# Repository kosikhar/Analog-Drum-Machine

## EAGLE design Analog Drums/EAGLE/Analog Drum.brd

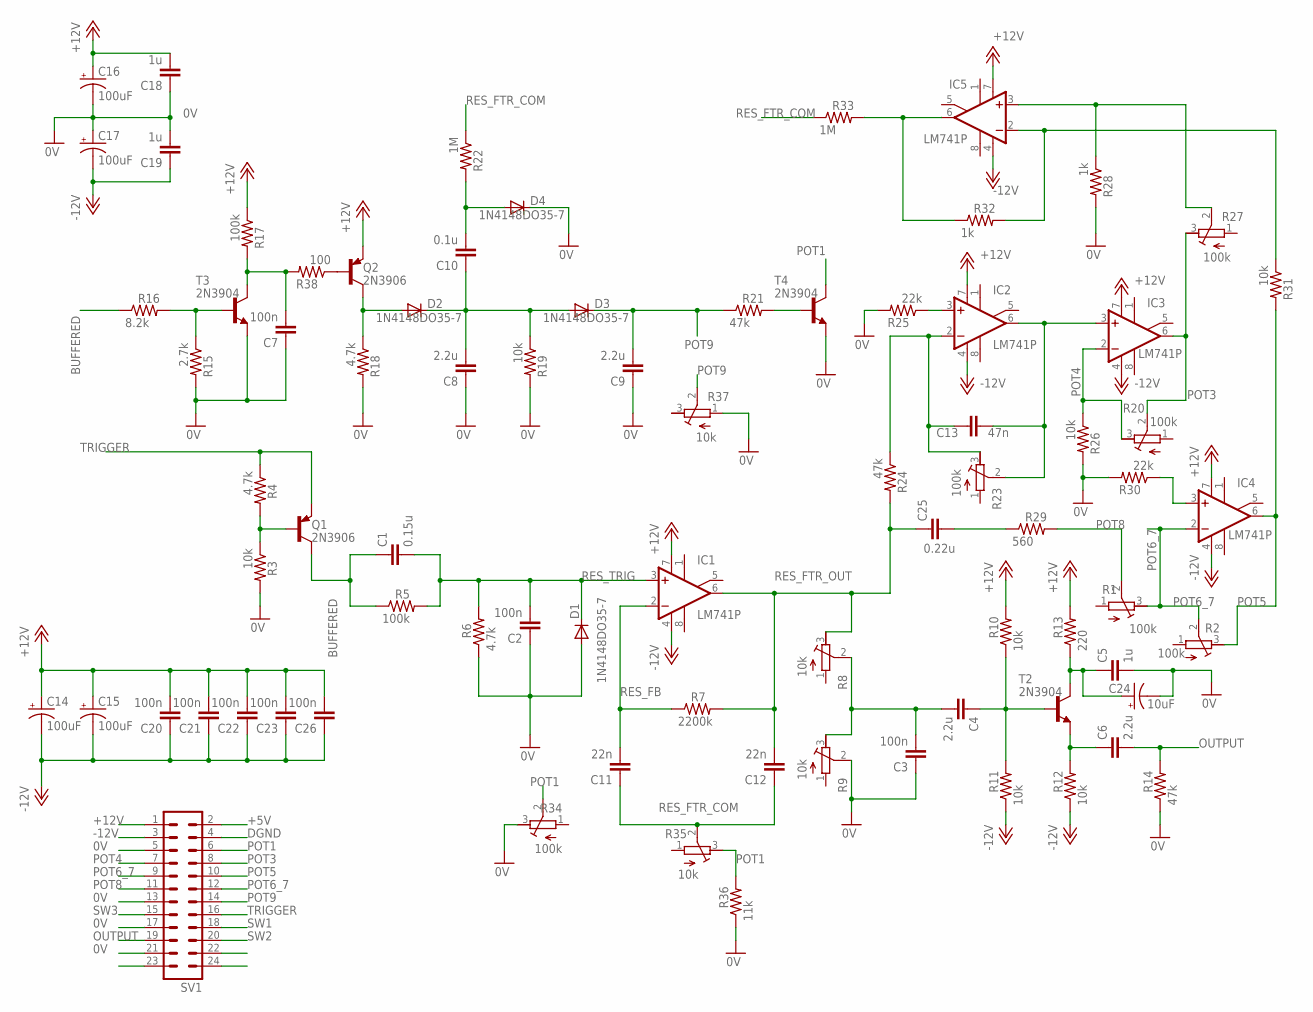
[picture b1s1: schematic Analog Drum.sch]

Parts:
C1: 0.15u; C050-024X044
C2, C3, C7, C20, C21, C22, C23, C26: 100n; C050-024X044
C4, C6, C8, C9: 2.2u; C050-024X044
C5, C18, C19: 1u; C050-024X044
C10: 0.1u; C050-024X044
C11, C12: 22n; C050-024X044
C13: 47n; C050-024X044
C14, C15, C16, C17: 100uF; E5-8,5
C24: 10uF; E2,5-6
C25: 0.22u; C050-024X044
D1, D2, D3, D4: 1N4148DO35-7; DO35-7
IC1, IC2, IC3, IC4, IC5: LM741P; DIL08
Q1, Q2: 2N3906; TO92
R1, R2, R20, R23, R27, R34: 100k; RTRIM64W
R3, R10, R11, R12, R19, R26, R31: 10k; 0207/10
R4, R6, R18: 4.7k; 0207/10
R5, R17: 100k; 0207/10
R7: 2200k; 0207/10
R8, R9, R35, R37: 10k; RTRIM64W
R13: 220; 0207/10
R14, R21, R24: 47k; 0207/10
R15: 2.7k; 0207/10
R16: 8.2k; 0207/10
R22, R33: 1M; 0207/10
R25, R30: 22k; 0207/10
R28, R32: 1k; 0207/10
R29: 560; 0207/10
R36: 11k; 0207/10
R38: 100; 0207/10
SV1: MA12-2
T2, T3, T4: 2N3904; TO92

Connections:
0V: C2.1, C3.1, C5.2, C7.1, C8.1, C9.1, C16.-, C17.+, C18.1, C19.2, C24.-, D1.A, D4.C, R3.2, R6.1, R9.2 (S), R14.1, R15.2, R18.2, R19.2, R25.2, R26.2, R28.2, R30.2, R34.3 (E), R36.1, R37.1 (A), SV1.5, SV1.13, SV1.17, SV1.21, T3.3 (E), T4.3 (E)
+5V: SV1.2
+12V: C14.+, C15.+, C16.+, C18.2, C20.2, C21.2, C22.2, C23.2, C26.2, IC1.7 (V+), IC2.7 (V+), IC3.7 (V+), IC4.7 (V+), IC5.7 (V+), Q2.3 (E), R10.2, R13.2, R17.1, SV1.1
-12V: C14.-, C15.-, C17.-, C19.1, C20.1, C21.1, C22.1, C23.1, C26.1, IC1.4 (V-), IC2.4 (V-), IC3.4 (V-), IC4.4 (V-), IC5.4 (V-), R11.1, R12.1, SV1.3
BUFFERED: C1.1, Q1.1 (C), R5.1, R16.1
DGND: SV1.4
unnamed: C25.2, R29.1
unnamed: IC4.3 (+IN), R30.1
unnamed: Q1.2 (B), R3.1, R4.2
unnamed: C10.2, D4.A, R22.2
unnamed: Q2.2 (B), R38.1
unnamed: IC2.3 (+IN), R25.1
unnamed: C3.2, C4.2, R8.2 (S), R9.3 (E)
unnamed: C4.1, R10.1, R11.2, T2.2 (B)
unnamed: C6.1, R12.2, T2.3 (E)
unnamed: C5.1, C24.+, R13.1, T2.1 (C)
unnamed: C13.2, IC2.2 (-IN), R23.3 (E), R24.1
unnamed: R15.1, R16.2, T3.2 (B)
unnamed: C7.2, R17.2, R38.2, T3.1 (C)
unnamed: D2.A, Q2.1 (C), R18.1
unnamed: C8.2, C10.1, D2.C, D3.A, R19.1
unnamed: R21.2, T4.2 (B)
unnamed: C13.1, IC2.6 (OUT), IC3.3 (+IN), R23.2 (S)
unnamed: IC5.3 (+IN), R27.2 (S), R28.1
unnamed: IC5.2 (-IN), R31.1, R32.2
unnamed: IC5.6 (OUT), R32.1, R33.2
OUTPUT: C6.2, R14.2, SV1.19
POT1: R34.2 (S), R35.3 (E), R36.2, SV1.6, T4.1 (C)
POT3: IC3.6 (OUT), R20.2 (S), R27.3 (E), SV1.8
POT4: IC3.2 (-IN), R20.3 (E), R26.1, SV1.7
POT5: IC4.6 (OUT), R2.3 (E), R31.2, SV1.10
POT6_7: IC4.2 (-IN), R1.3 (E), R2.2 (S), SV1.9, SV1.12
POT8: R1.2 (S), R29.2, SV1.11
POT9: C9.2, D3.C, R21.1, R37.2 (S), SV1.14
RES_FB: C11.2, IC1.2 (-IN), R7.1
RES_FTR_COM: C11.1, C12.1, R22.1, R33.1, R35.2 (S)
RES_FTR_OUT: C12.2, C25.1, IC1.6 (OUT), R7.2, R8.3 (E), R24.2
RES_TRIG: C1.2, C2.2, D1.C, IC1.3 (+IN), R5.2, R6.2
SW1: SV1.18
SW2: SV1.20
SW3: SV1.15
TRIGGER: Q1.3 (E), R4.1, SV1.16

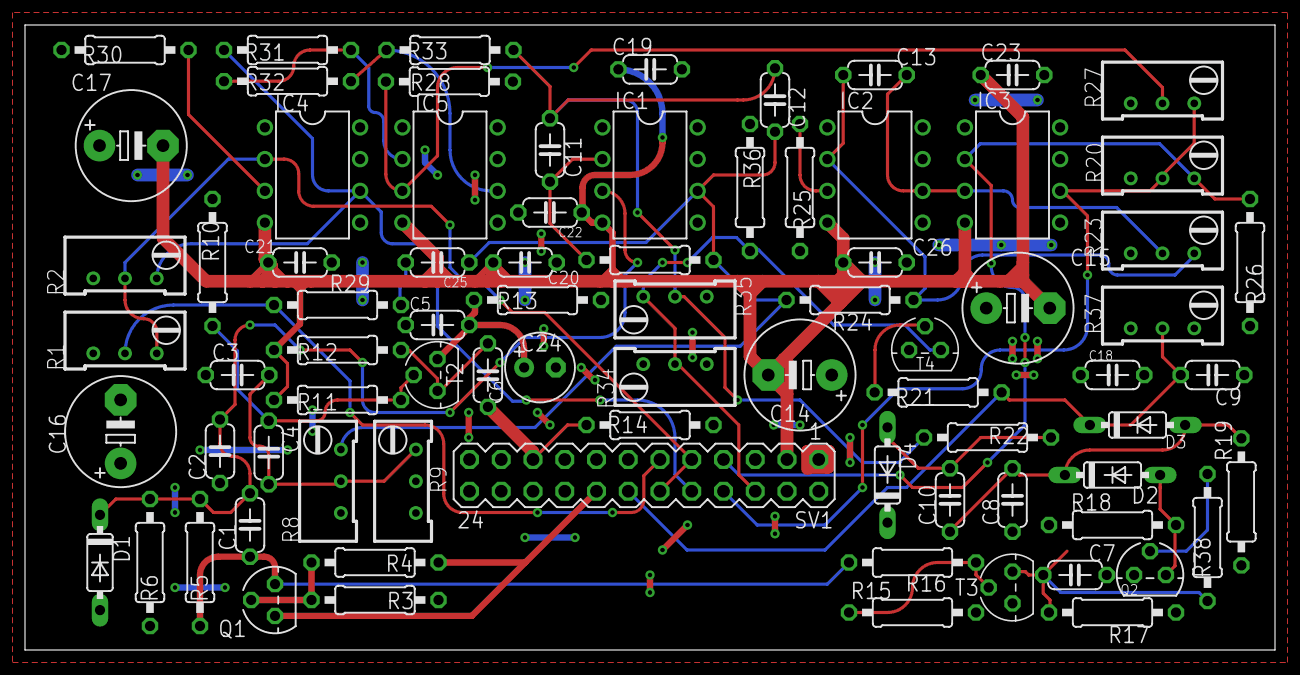
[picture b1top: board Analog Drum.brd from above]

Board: 2 copper layers, 100.0 x 50.0 mm, 79 parts (0 on the bottom side), 37 nets.

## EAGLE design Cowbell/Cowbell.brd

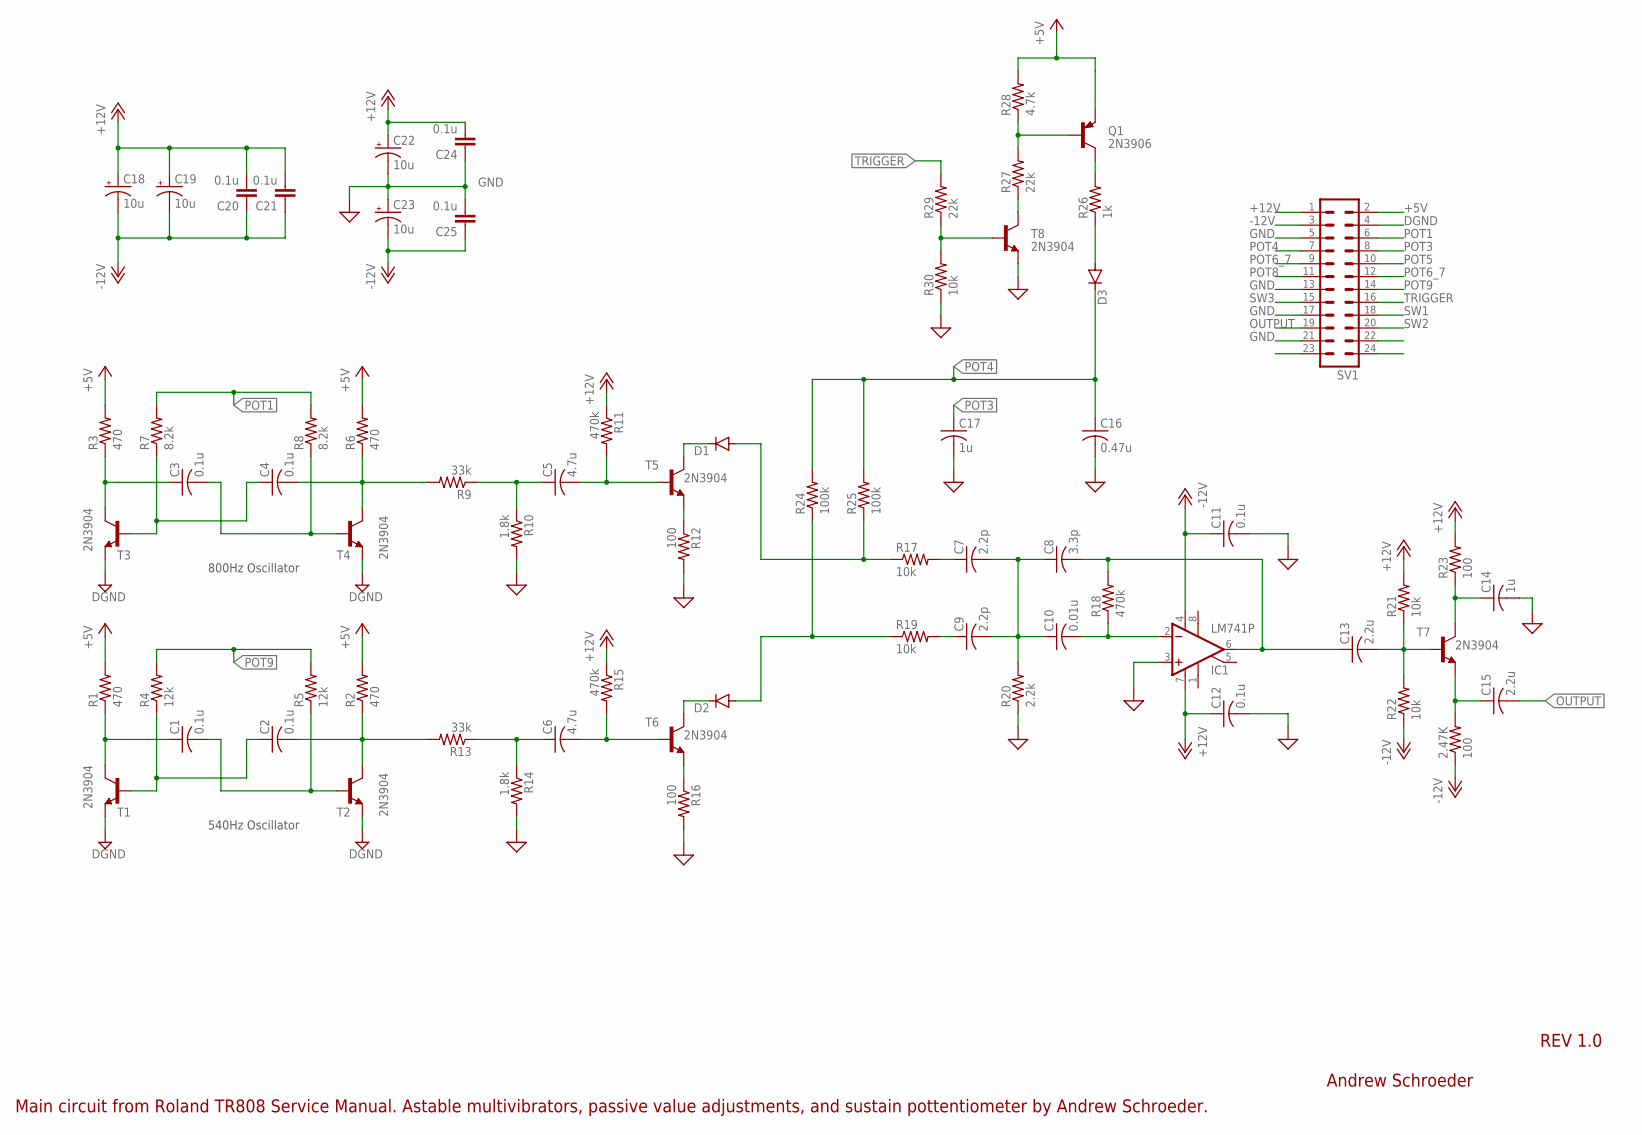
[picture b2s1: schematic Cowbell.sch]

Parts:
2.47K: 100; 0207/7
C1, C2, C3, C4, C11, C12: 0.1u; C025-024X044
C5, C6: 4.7u; C025-024X044
C7, C9: 2.2p; C025-024X044
C8: 3.3p; C025-024X044
C10: 0.01u; C025-024X044
C13, C15: 2.2u; C025-024X044
C14, C17: 1u; C025-024X044
C16: 0.47u; C025-024X044
C18, C19, C22, C23: 10u; E2,5-6
C20, C21, C24, C25: 0.1u; C050-024X044
D1, D2, D3: 1N4148DO35-7; DO35-7
IC1: LM741P; DIL08
Q1: 2N3906; TO92
R1, R2, R3, R6: 470; 0207/7
R4, R5: 12k; 0207/7
R7, R8: 8.2k; 0207/7
R9, R13: 33k; 0207/7
R10, R14: 1.8k; 0207/7
R11, R15, R18: 470k; 0207/7
R12, R16, R23: 100; 0207/7
R17, R19, R21, R22, R30: 10k; 0207/7
R20: 2.2k; 0207/7
R24, R25: 100k; 0207/7
R26: 1k; 0207/7
R27, R29: 22k; 0207/7
R28: 4.7k; 0207/7
SV1: MA12-2
T1, T2, T3, T4, T5, T6, T7, T8: 2N3904; TO92

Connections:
+5V: Q1.3 (E), R1.2, R2.2, R3.2, R6.2, R28.2, SV1.2
+12V: C12.1, C18.+, C19.+, C20.2, C21.2, C22.+, C24.2, IC1.7 (V+), R11.1, R15.1, R21.2, R23.2, SV1.1
-12V: 2.47K.1, C11.1, C18.-, C19.-, C20.1, C21.1, C23.-, C25.1, IC1.4 (V-), R22.1, SV1.3; also elsewhere on the board
DGND: SV1.4, T1.3 (E), T2.3 (E), T3.3 (E), T4.3 (E)
GND: C11.2, C12.2, C14.2, C16.2, C17.2, C22.-, C23.+, C24.1, C25.2, IC1.3 (+IN), R10.2, R12.2, R14.2, R16.2, R20.1, R30.1, SV1.5, SV1.13, SV1.17, SV1.21, T8.3 (E)
unnamed: C4.2, R6.1, R9.2, T4.1 (C)
unnamed: C2.2, R2.1, R13.2, T2.1 (C)
unnamed: C1.1, R1.1, T1.1 (C)
unnamed: C2.1, R4.1, T1.2 (B)
unnamed: C3.1, R3.1, T3.1 (C)
unnamed: C4.1, R7.1, T3.2 (B)
unnamed: C1.2, R5.1, T2.2 (B)
unnamed: C3.2, R8.1, T4.2 (B)
unnamed: C5.1, R9.1, R10.1
unnamed: D1.C, T5.1 (C)
unnamed: C5.2, R11.2, T5.2 (B)
unnamed: R12.1, T5.3 (E)
unnamed: C6.1, R13.1, R14.1
unnamed: C6.2, R15.2, T6.2 (B)
unnamed: R16.1, T6.3 (E)
unnamed: D2.C, T6.1 (C)
unnamed: D1.A, R17.1, R25.1
unnamed: D2.A, R19.1, R24.1
unnamed: C7.1, R17.2
unnamed: C7.2, C8.1, C9.2, C10.1, R20.2
unnamed: C8.2, C13.1, IC1.6 (OUT), R18.2
unnamed: C10.2, IC1.2 (-IN), R18.1
unnamed: C13.2, R21.1, R22.2, T7.2 (B)
unnamed: C9.1, R19.2
unnamed: Q1.1 (C), R26.2
unnamed: C14.1, R23.1, T7.1 (C)
unnamed 34: 2.47K.2, C15.1, T7.3 (E); also elsewhere on the board
unnamed: R27.1, T8.1 (C)
unnamed: D3.A, R26.1
unnamed: R29.1, R30.2, T8.2 (B)
unnamed: Q1.2 (B), R27.2, R28.1
OUTPUT: C15.2, SV1.19
POT1: R7.2, R8.2, SV1.6
POT3: C17.1, SV1.8
POT4: C16.1, D3.C, R24.2, R25.2, SV1.7
POT5: SV1.10
POT6_7: SV1.9, SV1.12
POT8: SV1.11
POT9: R4.2, R5.2, SV1.14
SW1: SV1.18
SW2: SV1.20
SW3: SV1.15
TRIGGER: R29.2, SV1.16

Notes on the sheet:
540Hz Oscillator
800Hz Oscillator
Andrew Schroeder
REV 1.0
Main circuit from Roland TR808 Service Manual. Astable multivibrators, passive value adjustments, and sustain pottentiometer by Andrew Schroeder.

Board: 2 copper layers, 75 parts (0 on the bottom side), 43 nets, no tracks yet.

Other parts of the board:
R31: 2.47k; 0207/7
U$1, U$2, U$3, U$4: STAND-OFF
U$6: A5L-LOC

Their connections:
-12V: R31.1; also elsewhere on the board
unnamed 34: R31.2; also elsewhere on the board

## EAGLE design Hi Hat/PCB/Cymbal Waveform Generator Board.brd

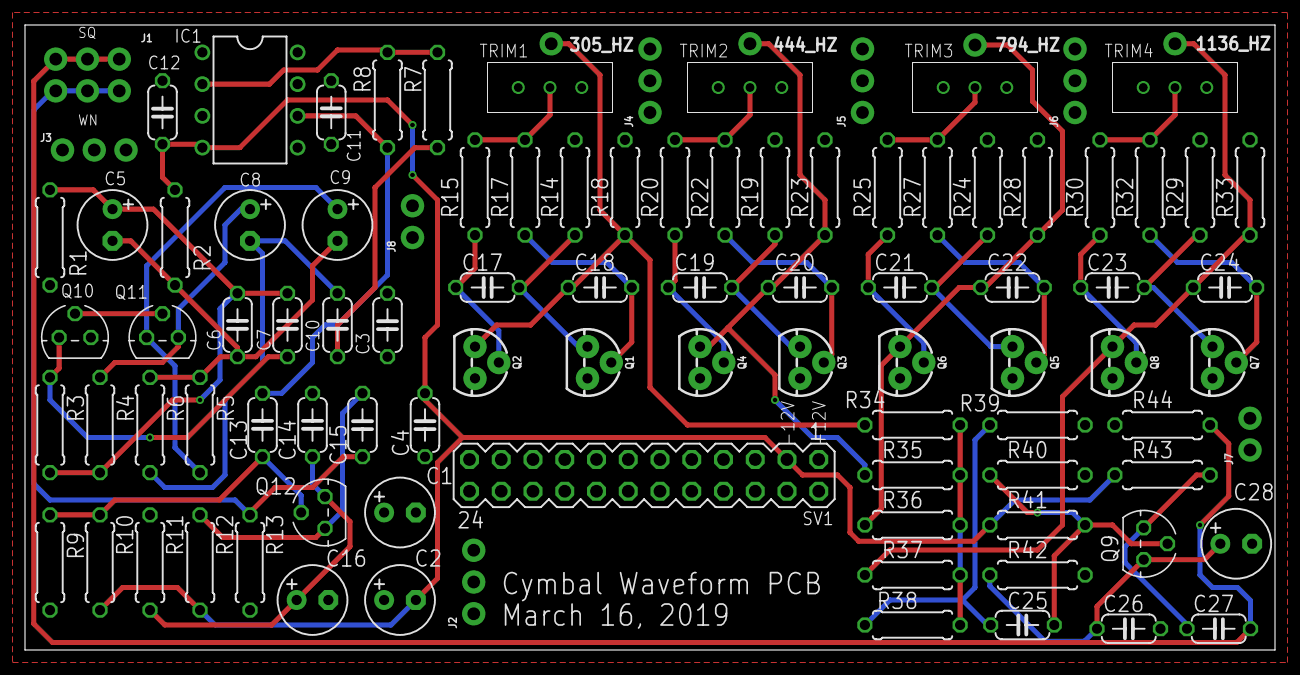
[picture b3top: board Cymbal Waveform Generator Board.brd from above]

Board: 2 copper layers, 100.0 x 50.0 mm, 98 parts (0 on the bottom side), 43 nets.

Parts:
305_HZ, 444_HZ, 794_HZ, 1136_HZ: 1X01NS_KIT
C1, C2, C5, C8, C9, C16, C28: 10uF; E2,5-6
C3, C4, C14, C26: 1u; C050-024X044
C6, C7, C10, C11, C12, C17, C18, C19, C20: 0.1uF; C050-024X044
C13, C15, C25, C27: 2.2u; C050-024X044
C21, C22: 47nF; C050-024X044
C23, C24: 33nF; C050-024X044
IC1: LM741P; DIL08
J1: 2X3-NS
J2, J3, J4, J5, J6: 1X03_NO_SILK
J7, J8: 1X02_NO_SILK
Q1, Q2, Q3, Q4, Q5, Q6, Q7, Q8: 2N2222A; TO-92
Q9, Q10, Q11, Q12: 2N3904; TO92
R1, R2: 2k; 0207/7
R3: 680k; 0207/7
R4: 4.7k; 0207/7
R5: 1k; 0207/7
R6, R8: 100k; 0207/7
R7: 68k; 0207/7
R9, R10, R12, R14, R18, R19, R23, R24, R28, R29, R33, R39, R40, R41, R43: 10k; 0207/7
R11, R42: 220; 0207/7
R13, R38, R44: 47k; 0207/7
R15, R17, R20, R22, R25, R27, R30, R32: 20k; 0207/7
R34, R35, R36, R37: 220k; 0207/7
SV1: MA12-2
TRIM1, TRIM2, TRIM3, TRIM4: 10k; 10K_TRIM

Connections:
+12V: C1.+, C3.2, C11.2, IC1.7, R1.2, R9.2, R11.2, R14.2, R18.2, R19.2, R23.2, R24.2, R28.2, R29.2, R33.2, R40.2, R42.2, SV1.1, TRIM1.P$3, TRIM2.P$3, TRIM3.P$3, TRIM4.P$3
-12V: C2.-, C4.1, C12.2, IC1.4, R2.2, R10.1, R12.1, R41.1, R43.1, SV1.3
AGND: C1.-, C2.+, C3.1, C4.2, C11.1, C12.1, C14.2, C16.-, C26.2, C28.-, IC1.3, Q1.3, Q2.3, Q3.3, Q4.3, Q5.3, Q6.3, Q7.3, Q8.3, R13.1, R39.1, R44.1, SV1.17, SV1.21
unnamed: C13.1, Q12.2, R9.1, R10.2
unnamed: C15.1, Q12.3, R12.2
unnamed: C14.1, C16.+, Q12.1, R11.1
unnamed: C9.+, Q11.3, R5.2
unnamed: C5.+, C6.2, C7.2, R1.1, R3.2, R4.2
unnamed: C13.2, IC1.6, R8.1
unnamed: C17.2, Q1.1, R14.1
unnamed: C17.1, Q2.2, R15.1
unnamed: C18.2, Q1.2, R17.1
unnamed: R15.2, R17.2, TRIM1.P$2
unnamed: C19.2, Q3.1, R19.1
unnamed: Q10.2, Q11.2
unnamed: C19.1, Q4.2, R20.1
unnamed: C20.2, Q3.2, R22.1
unnamed: C7.1, Q10.3, R3.1
unnamed: C5.-, C6.1, C9.-, R2.1, R5.1, R6.1
unnamed: R34.2, R35.2, R36.2, R37.2, R38.1
unnamed: IC1.2, R7.1, R8.2
unnamed: C10.1, R7.2
unnamed: R20.2, R22.2, TRIM2.P$2
unnamed: C8.+, Q11.1, R4.1
unnamed: C21.2, Q5.1, R24.1
unnamed: C21.1, Q6.2, R25.1
unnamed: C22.2, Q5.2, R27.1
unnamed: R25.2, R27.2, TRIM3.P$2
unnamed: C23.2, Q7.1, R29.1
unnamed: C23.1, Q8.2, R30.1
unnamed: C24.2, Q7.2, R32.1
unnamed: C25.2, R38.2, R39.2
unnamed: R30.2, R32.2, TRIM4.P$2
unnamed: C25.1, Q9.2, R40.1, R41.2
unnamed: C27.1, Q9.3, R43.2
unnamed: C26.1, C28.+, Q9.1, R42.1
OSC1: 305_HZ.1, C18.1, Q2.1, R18.1, R34.1
OSC2: 444_HZ.1, C20.1, Q4.1, R23.1, R35.1
OSC3: 794_HZ.1, C22.1, Q6.1, R28.1, R36.1
OSC4: 1136_HZ.1, C24.1, Q8.1, R33.1, R37.1
SQUARE_WAVE_BUFFERED: C27.2, J1.2, J1.4, J1.6, R44.2
WHITE_NOISE: C8.-, C10.2, R6.2
WHITE_NOISE_BUFFERED: C15.2, J1.1, J1.3, J1.5, R13.2

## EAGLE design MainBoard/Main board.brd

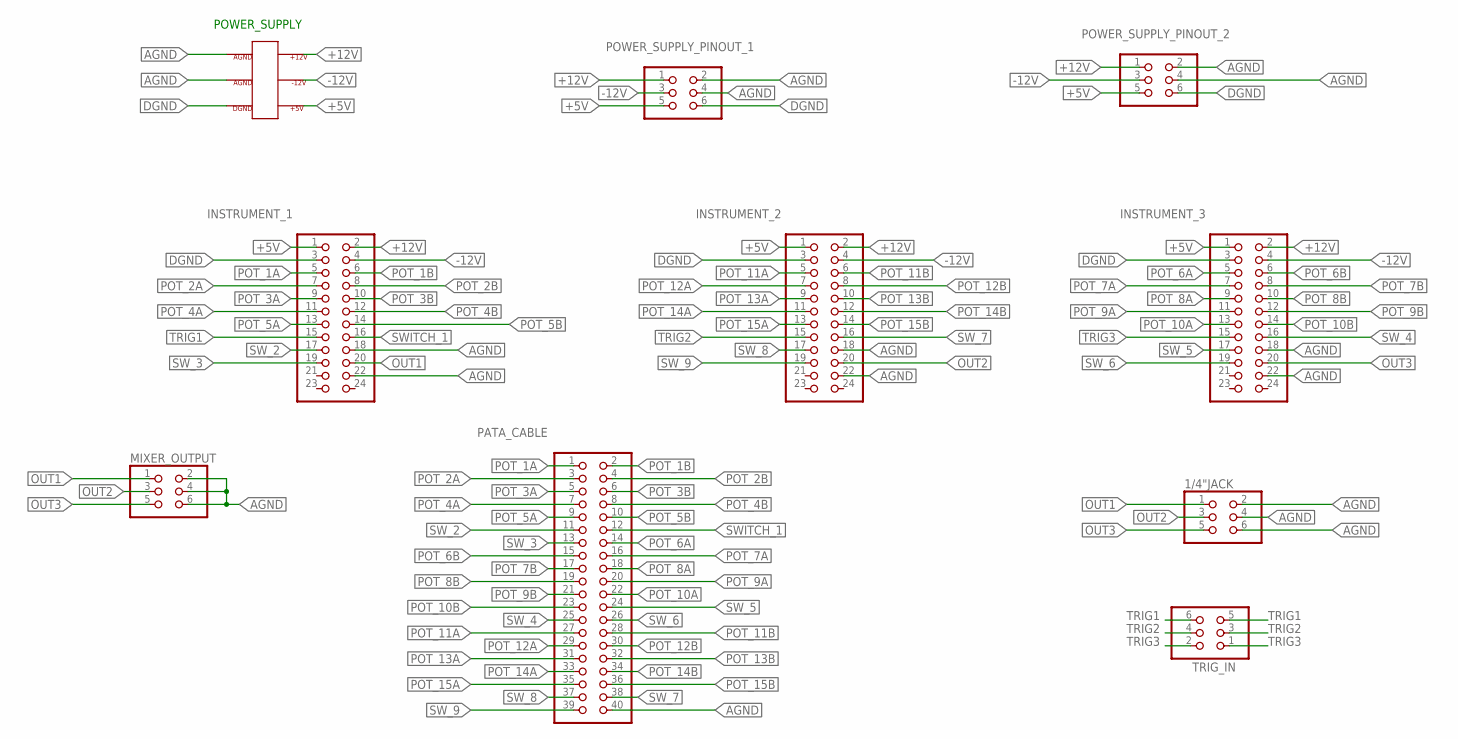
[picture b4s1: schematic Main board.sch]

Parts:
1/4"JACK: PINHD-2X3; 2X03
INSTRUMENT_1, INSTRUMENT_2, INSTRUMENT_3: PINHD-2X12; 2X12
MIXER_OUTPUT: PINHD-2X3; 2X03
PATA_CABLE: PINHD-2X20; 2X20
POWER_SUPPLY: TER6PIN_VERT; CAPSTONE_1-770875-0
POWER_SUPPLY_PINOUT_1, POWER_SUPPLY_PINOUT_2: PINHD-2X3; 2X03
TRIG_IN: PINHD-2X3; 2X03

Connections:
+5V: INSTRUMENT_1.1, INSTRUMENT_2.1, INSTRUMENT_3.1, POWER_SUPPLY.+5V, POWER_SUPPLY.NULL (+5V), POWER_SUPPLY_PINOUT_1.5, POWER_SUPPLY_PINOUT_2.5
+12V: INSTRUMENT_1.2, INSTRUMENT_2.2, INSTRUMENT_3.2, POWER_SUPPLY.+12V, POWER_SUPPLY_PINOUT_1.1, POWER_SUPPLY_PINOUT_2.1
-12V: INSTRUMENT_1.4, INSTRUMENT_2.4, INSTRUMENT_3.4, POWER_SUPPLY.-12V, POWER_SUPPLY_PINOUT_1.3, POWER_SUPPLY_PINOUT_2.3
AGND: 1/4"JACK.2, 1/4"JACK.4, 1/4"JACK.6, INSTRUMENT_1.18, INSTRUMENT_1.22, INSTRUMENT_2.18, INSTRUMENT_2.22, INSTRUMENT_3.18, INSTRUMENT_3.22, MIXER_OUTPUT.2, MIXER_OUTPUT.4, MIXER_OUTPUT.6, PATA_CABLE.40, POWER_SUPPLY.AGND0, POWER_SUPPLY.AGND1, POWER_SUPPLY_PINOUT_1.2, POWER_SUPPLY_PINOUT_1.4, POWER_SUPPLY_PINOUT_2.2, POWER_SUPPLY_PINOUT_2.4
DGND: INSTRUMENT_1.3, INSTRUMENT_2.3, INSTRUMENT_3.3, POWER_SUPPLY.DGND, POWER_SUPPLY_PINOUT_1.6, POWER_SUPPLY_PINOUT_2.6
OUT1: 1/4"JACK.1, INSTRUMENT_1.20, MIXER_OUTPUT.1
OUT2: 1/4"JACK.3, INSTRUMENT_2.20, MIXER_OUTPUT.3
OUT3: 1/4"JACK.5, INSTRUMENT_3.20, MIXER_OUTPUT.5
POT_1A: INSTRUMENT_1.5, PATA_CABLE.1
POT_1B: INSTRUMENT_1.6, PATA_CABLE.2
POT_2A: INSTRUMENT_1.7, PATA_CABLE.3
POT_2B: INSTRUMENT_1.8, PATA_CABLE.4
POT_3A: INSTRUMENT_1.9, PATA_CABLE.5
POT_3B: INSTRUMENT_1.10, PATA_CABLE.6
POT_4A: INSTRUMENT_1.11, PATA_CABLE.7
POT_4B: INSTRUMENT_1.12, PATA_CABLE.8
POT_5A: INSTRUMENT_1.13, PATA_CABLE.9
POT_5B: INSTRUMENT_1.14, PATA_CABLE.10
POT_6A: INSTRUMENT_3.5, PATA_CABLE.14
POT_6B: INSTRUMENT_3.6, PATA_CABLE.15
POT_7A: INSTRUMENT_3.7, PATA_CABLE.16
POT_7B: INSTRUMENT_3.8, PATA_CABLE.17
POT_8A: INSTRUMENT_3.9, PATA_CABLE.18
POT_8B: INSTRUMENT_3.10, PATA_CABLE.19
POT_9A: INSTRUMENT_3.11, PATA_CABLE.20
POT_9B: INSTRUMENT_3.12, PATA_CABLE.21
POT_10A: INSTRUMENT_3.13, PATA_CABLE.22
POT_10B: INSTRUMENT_3.14, PATA_CABLE.23
POT_11A: INSTRUMENT_2.5, PATA_CABLE.27
POT_11B: INSTRUMENT_2.6, PATA_CABLE.28
POT_12A: INSTRUMENT_2.7, PATA_CABLE.29
POT_12B: INSTRUMENT_2.8, PATA_CABLE.30
POT_13A: INSTRUMENT_2.9, PATA_CABLE.31
POT_13B: INSTRUMENT_2.10, PATA_CABLE.32
POT_14A: INSTRUMENT_2.11, PATA_CABLE.33
POT_14B: INSTRUMENT_2.12, PATA_CABLE.34
POT_15A: INSTRUMENT_2.13, PATA_CABLE.35
POT_15B: INSTRUMENT_2.14, PATA_CABLE.36
SWITCH_1: INSTRUMENT_1.16, PATA_CABLE.12
SW_2: INSTRUMENT_1.17, PATA_CABLE.11
SW_3: INSTRUMENT_1.19, PATA_CABLE.13
SW_4: INSTRUMENT_3.16, PATA_CABLE.25
SW_5: INSTRUMENT_3.17, PATA_CABLE.24
SW_6: INSTRUMENT_3.19, PATA_CABLE.26
SW_7: INSTRUMENT_2.16, PATA_CABLE.38
SW_8: INSTRUMENT_2.17, PATA_CABLE.37
SW_9: INSTRUMENT_2.19, PATA_CABLE.39
TRIG1: INSTRUMENT_1.15, TRIG_IN.5, TRIG_IN.6
TRIG2: INSTRUMENT_2.15, TRIG_IN.3, TRIG_IN.4
TRIG3: INSTRUMENT_3.15, TRIG_IN.1, TRIG_IN.2

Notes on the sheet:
POWER_SUPPLY

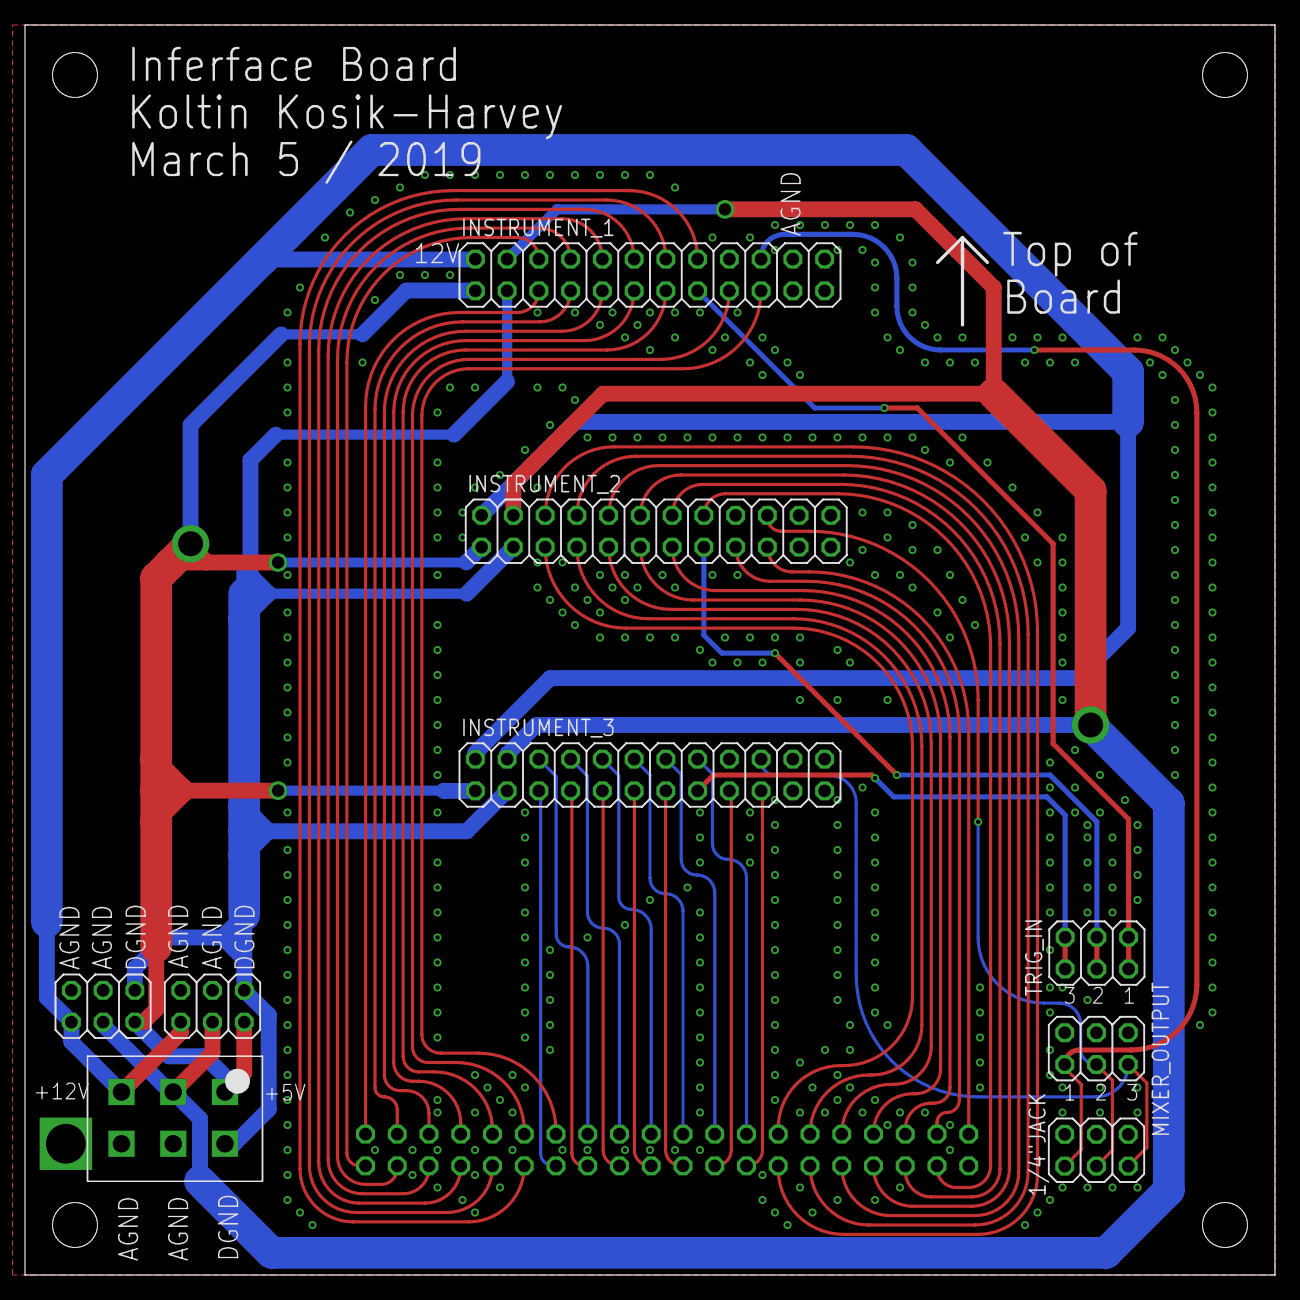
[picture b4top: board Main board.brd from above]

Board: 2 copper layers, 100.0 x 100.0 mm, 10 parts (1 on the bottom side), 50 nets.

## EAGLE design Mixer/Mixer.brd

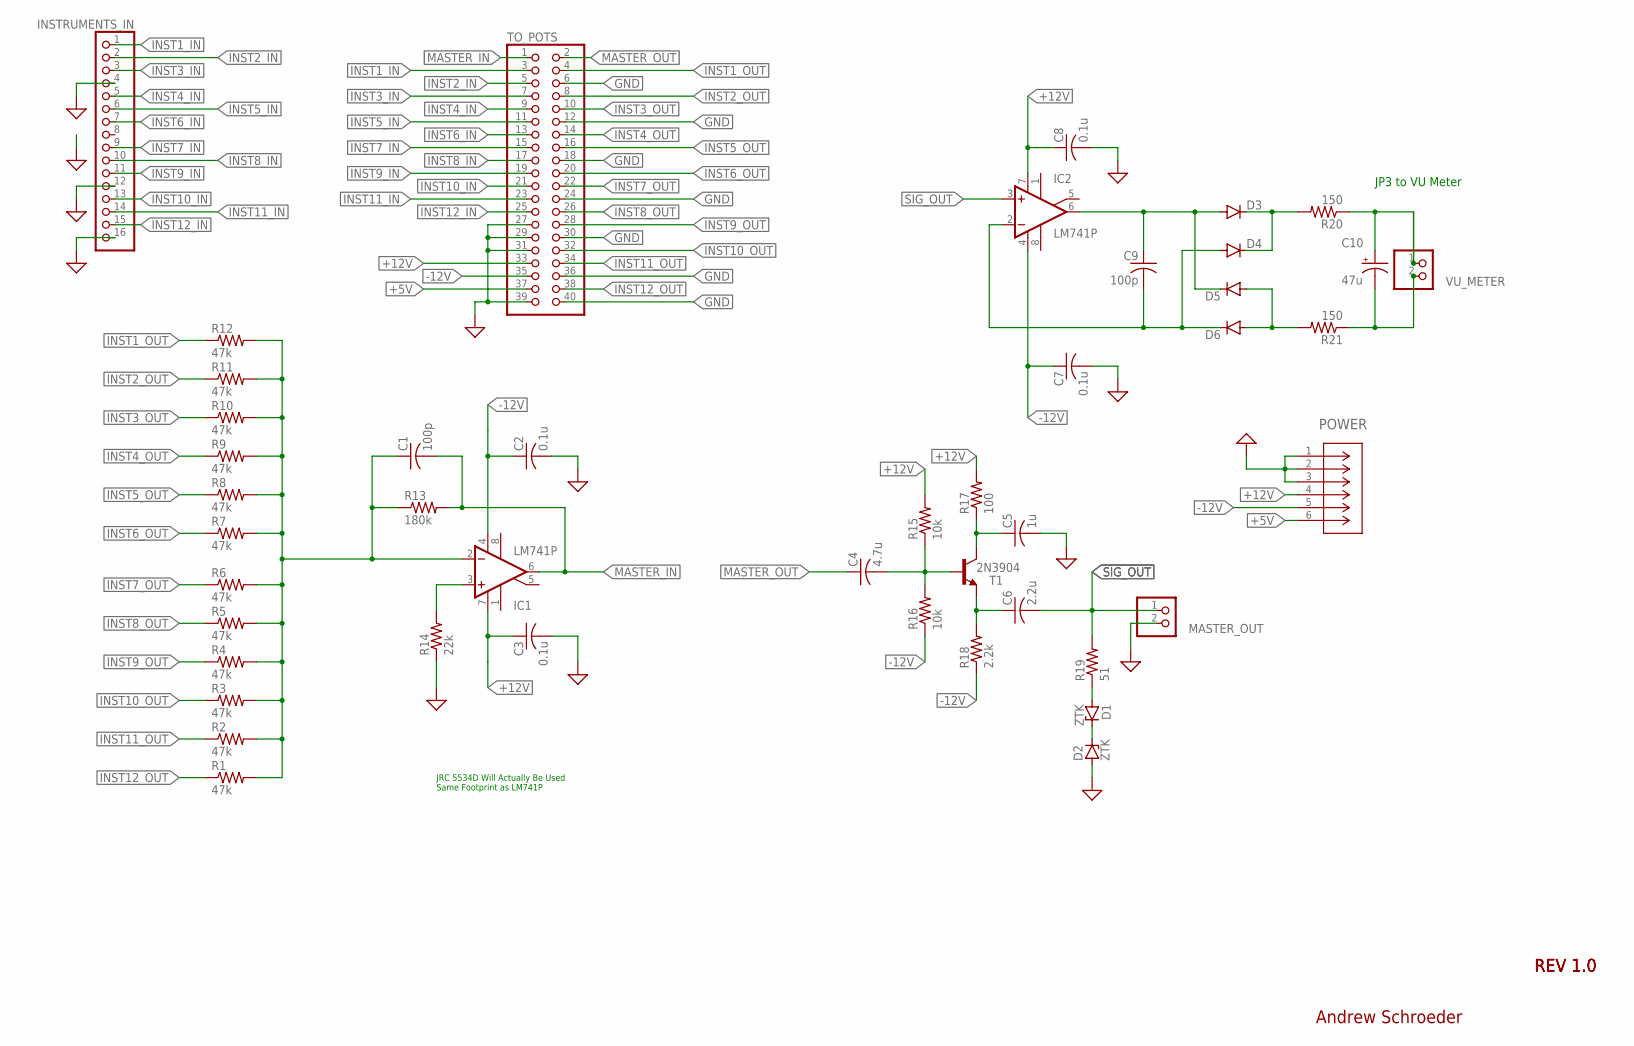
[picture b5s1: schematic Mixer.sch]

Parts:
C1, C9: 100p; C025-025X050
C2, C3, C7, C8: 0.1u; C025-025X050
C4: 4.7u; C025-025X050
C5: 1u; C025-025X050
C6: 2.2u; C025-025X050
C10: 47u; E2-5
D1, D2: ZTK; DO35Z10
D3, D4, D5, D6: 1N4148DO35-7; DO35-7
IC1, IC2: LM741P; DIL08
INSTRUMENTS_IN: PINHD-1X16; 1X16
MASTER_OUT: PINHD-1X2; 1X02
POWER: 1-770875-0; CON6_2X3_P163_RAMNL
R1, R2, R3, R4, R5, R6, R7, R8, R9, R10, R11, R12: 47k; 0207/7
R13: 180k; 0207/7
R14: 22k; 0207/7
R15, R16: 10k; 0207/7
R17: 100; 0207/7
R18: 2.2k; 0207/7
R19: 51; 0207/7
R20, R21: 150; 0207/7
T1: 2N3904; TO92
TO_POTS: PINHD-2X20; 2X20
VU_METER: PINHD-1X2; 1X02

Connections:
+5V: POWER.6, TO_POTS.37
+12V: C3.1, C8.1, IC1.7 (V+), IC2.7 (V+), POWER.4, R15.2, R17.2, TO_POTS.33
-12V: C2.1, C7.1, IC1.4 (V-), IC2.4 (V-), POWER.5, R16.1, R18.1, TO_POTS.35
GND: C2.2, C3.2, C5.2, C7.2, C8.2, D2.A, INSTRUMENTS_IN.4, INSTRUMENTS_IN.12, INSTRUMENTS_IN.16, MASTER_OUT.2, POWER.1, POWER.2, POWER.3, R14.1, TO_POTS.6, TO_POTS.12, TO_POTS.18, TO_POTS.24, TO_POTS.27, TO_POTS.29, TO_POTS.30, TO_POTS.31, TO_POTS.36, TO_POTS.39, TO_POTS.40
INST1_IN: INSTRUMENTS_IN.1, TO_POTS.3
INST1_OUT: R12.1, TO_POTS.4
INST2_IN: INSTRUMENTS_IN.2, TO_POTS.5
INST2_OUT: R11.1, TO_POTS.8
INST3_IN: INSTRUMENTS_IN.3, TO_POTS.7
INST3_OUT: R10.1, TO_POTS.10
INST4_IN: INSTRUMENTS_IN.5, TO_POTS.9
INST4_OUT: R9.1, TO_POTS.14
INST5_IN: INSTRUMENTS_IN.6, TO_POTS.11
INST5_OUT: R8.1, TO_POTS.16
INST6_IN: INSTRUMENTS_IN.7, TO_POTS.13
INST6_OUT: R7.1, TO_POTS.20
INST7_IN: INSTRUMENTS_IN.9, TO_POTS.15
INST7_OUT: R6.1, TO_POTS.22
INST8_IN: INSTRUMENTS_IN.10, TO_POTS.17
INST8_OUT: R5.1, TO_POTS.26
INST9_IN: INSTRUMENTS_IN.11, TO_POTS.19
INST9_OUT: R4.1, TO_POTS.28
INST10_IN: INSTRUMENTS_IN.13, TO_POTS.21
INST10_OUT: R3.1, TO_POTS.32
INST11_IN: INSTRUMENTS_IN.14, TO_POTS.23
INST11_OUT: R2.1, TO_POTS.34
INST12_IN: INSTRUMENTS_IN.15, TO_POTS.25
INST12_OUT: R1.1, TO_POTS.38
MASTER_IN: C1.2, IC1.6 (OUT), R13.2, TO_POTS.1
MASTER_OUT: C4.1, TO_POTS.2
unnamed: C9.1, D3.A, D5.C, IC2.6 (OUT)
unnamed: IC1.3 (+IN), R14.2
unnamed: C9.2, D4.A, D6.C, IC2.2 (-IN)
unnamed: C1.1, IC1.2 (-IN), R1.2, R2.2, R3.2, R4.2, R5.2, R6.2, R7.2, R8.2, R9.2, R10.2, R11.2, R12.2, R13.1
unnamed: D5.A, D6.A, R21.2
unnamed: C4.2, R15.1, R16.2, T1.2 (B)
unnamed: C10.+, R20.1, VU_METER.1
unnamed: C5.1, R17.1, T1.1 (C)
unnamed: D3.C, D4.C, R20.2
unnamed: C6.1, R18.2, T1.3 (E)
unnamed: C10.-, R21.1, VU_METER.2
unnamed: D1.A, R19.1
unnamed: D1.C, D2.C
SIG_OUT: C6.2, IC2.3 (+IN), MASTER_OUT.1, R19.2

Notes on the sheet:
JRC 5534D Will Actually Be Used Same Footprint as LM741P
JP3 to VU Meter
REV 1.0
Andrew Schroeder

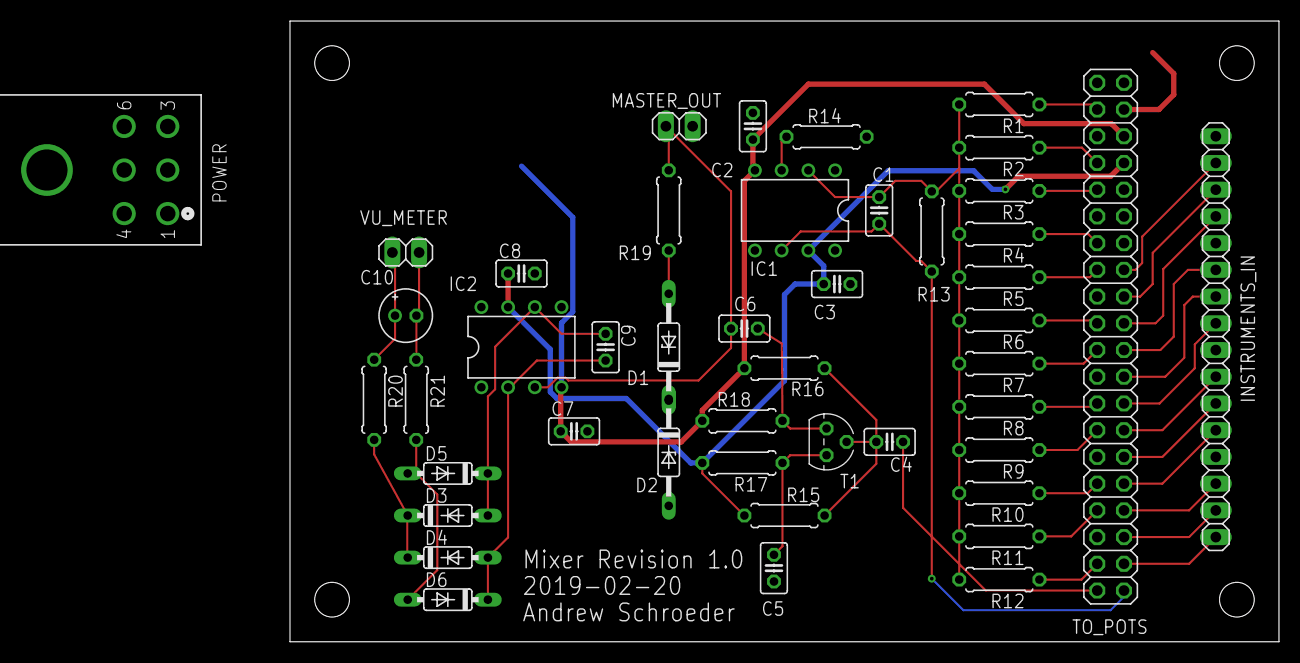
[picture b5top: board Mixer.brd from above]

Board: 2 copper layers, 94.0 x 59.0 mm, 49 parts (0 on the bottom side), 44 nets.

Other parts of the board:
U$1, U$2, U$3, U$4: STAND-OFF

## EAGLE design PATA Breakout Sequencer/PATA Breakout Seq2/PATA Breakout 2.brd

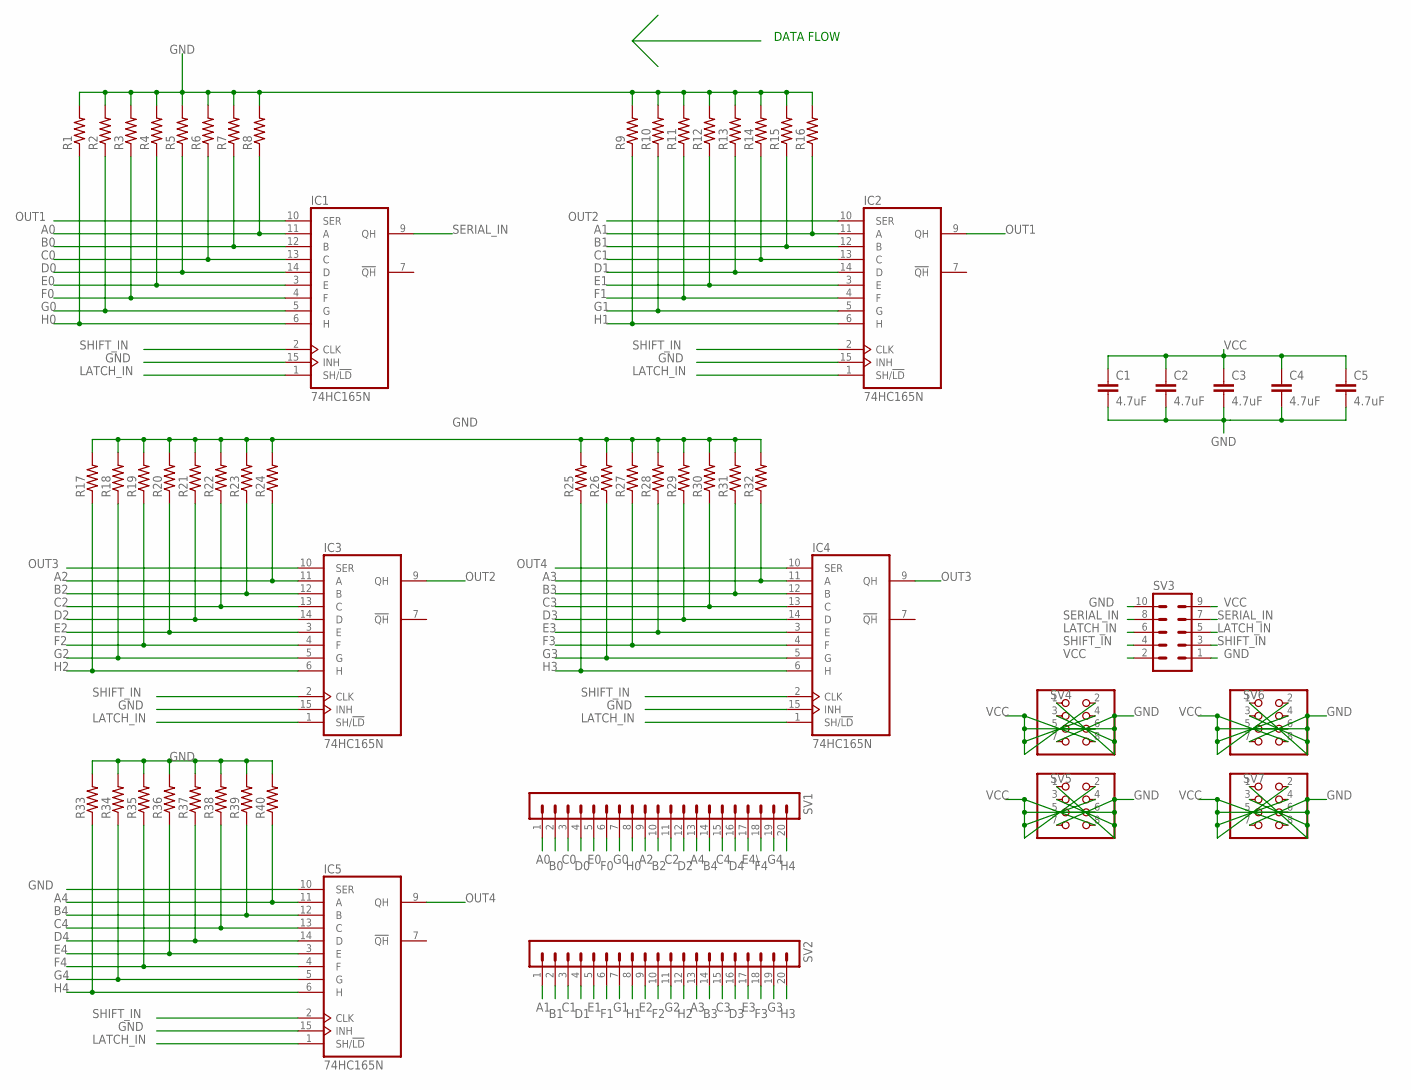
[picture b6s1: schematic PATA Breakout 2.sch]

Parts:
C1, C2, C3, C4, C5: 4.7uF; C050-024X044
IC1, IC2, IC3, IC4, IC5: 74HC165N; DIL16
R1, R2, R3, R4, R5, R6, R7, R8, R9, R10, R11, R12, R13, R14, R15, R16, R17, R18, R19, R20, R21, R22, R23, R24, R25, R26, R27, R28, R29, R30, R31, R32, R33, R34, R35, R36, R37, R38, R39, R40: R-US_0204/5; 0204/5
SV1, SV2: MA20-1
SV3: MA05-2
SV4, SV5, SV6, SV7: PINHD-2X4; 2X04

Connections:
A0: IC1.11 (A), R8.1, SV1.1
A1: IC2.11 (A), R16.1, SV2.1
A2: IC3.11 (A), R24.1, SV1.9
A3: IC4.11 (A), R32.1, SV2.13
A4: IC5.11 (A), R40.1, SV1.13
B0: IC1.12 (B), R7.1, SV1.2
B1: IC2.12 (B), R15.1, SV2.2
B2: IC3.12 (B), R23.1, SV1.10
B3: IC4.12 (B), R31.1, SV2.14
B4: IC5.12 (B), R39.1, SV1.14
C0: IC1.13 (C), R6.1, SV1.3
C1: IC2.13 (C), R14.1, SV2.3
C2: IC3.13 (C), R22.1, SV1.11
C3: IC4.13 (C), R30.1, SV2.15
C4: IC5.13 (C), R38.1, SV1.15
D0: IC1.14 (D), R5.1, SV1.4
D1: IC2.14 (D), R13.1, SV2.4
D2: IC3.14 (D), R21.1, SV1.12
D3: IC4.14 (D), R29.1, SV2.16
D4: IC5.14 (D), R37.1, SV1.16
E0: IC1.3 (E), R4.1, SV1.5
E1: IC2.3 (E), R12.1, SV2.5
E2: IC3.3 (E), R20.1, SV2.9
E3: IC4.3 (E), R28.1, SV2.17
E4: IC5.3 (E), R36.1
E4\: SV1.17
F0: IC1.4 (F), R3.1, SV1.6
F1: IC2.4 (F), R11.1, SV2.6
F2: IC3.4 (F), R19.1, SV2.10
F3: IC4.4 (F), R27.1, SV2.18
F4: IC5.4 (F), R35.1, SV1.18
G0: IC1.5 (G), R2.1, SV1.7
G1: IC2.5 (G), R10.1, SV2.7
G2: IC3.5 (G), R18.1, SV2.11
G3: IC4.5 (G), R26.1, SV2.19
G4: IC5.5 (G), R34.1, SV1.19
GND: C1.2, C2.2, C3.2, C4.2, C5.2, IC1.8 (GND), IC1.15 (INH), IC2.8 (GND), IC2.15 (INH), IC3.8 (GND), IC3.15 (INH), IC4.8 (GND), IC4.15 (INH), IC5.8 (GND), IC5.10 (SER), IC5.15 (INH), R1.2, R2.2, R3.2, R4.2, R5.2, R6.2, R7.2, R8.2, R9.2, R10.2, R11.2, R12.2, R13.2, R14.2, R15.2, R16.2, R17.2, R18.2, R19.2, R20.2, R21.2, R22.2, R23.2, R24.2, R25.2, R26.2, R27.2, R28.2, R29.2, R30.2, R31.2, R32.2, R33.2, R34.2, R35.2, R36.2, R37.2, R38.2, R39.2, R40.2, SV3.1, SV3.10, SV4.1, SV4.3, SV4.5, SV4.7, SV5.1, SV5.3, SV5.5, SV5.7, SV6.1, SV6.3, SV6.5, SV6.7, SV7.1, SV7.3, SV7.5, SV7.7
H0: IC1.6 (H), R1.1, SV1.8
H1: IC2.6 (H), R9.1, SV2.8
H2: IC3.6 (H), R17.1, SV2.12
H3: IC4.6 (H), R25.1, SV2.20
H4: IC5.6 (H), R33.1, SV1.20
LATCH_IN: IC1.1 (SH/!LD), IC2.1 (SH/!LD), IC3.1 (SH/!LD), IC4.1 (SH/!LD), IC5.1 (SH/!LD), SV3.5, SV3.6
OUT1: IC1.10 (SER), IC2.9 (QH)
OUT2: IC2.10 (SER), IC3.9 (QH)
OUT3: IC3.10 (SER), IC4.9 (QH)
OUT4: IC4.10 (SER), IC5.9 (QH)
SERIAL_IN: IC1.9 (QH), SV3.7, SV3.8
SHIFT_IN: IC1.2 (CLK), IC2.2 (CLK), IC3.2 (CLK), IC4.2 (CLK), IC5.2 (CLK), SV3.3, SV3.4
VCC: C1.1, C2.1, C3.1, C4.1, C5.1, IC1.16 (VCC), IC2.16 (VCC), IC3.16 (VCC), IC4.16 (VCC), IC5.16 (VCC), SV3.2, SV3.9, SV4.2, SV4.4, SV4.6, SV4.8, SV5.2, SV5.4, SV5.6, SV5.8, SV6.2, SV6.4, SV6.6, SV6.8, SV7.2, SV7.4, SV7.6, SV7.8

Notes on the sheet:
DATA FLOW

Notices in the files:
parts and their libraries:
SparkFun-DiscreteSemi: Licensing: Creative Commons ShareAlike 4.0 International - https://creativecommons.org/licenses/by-sa/4.0
